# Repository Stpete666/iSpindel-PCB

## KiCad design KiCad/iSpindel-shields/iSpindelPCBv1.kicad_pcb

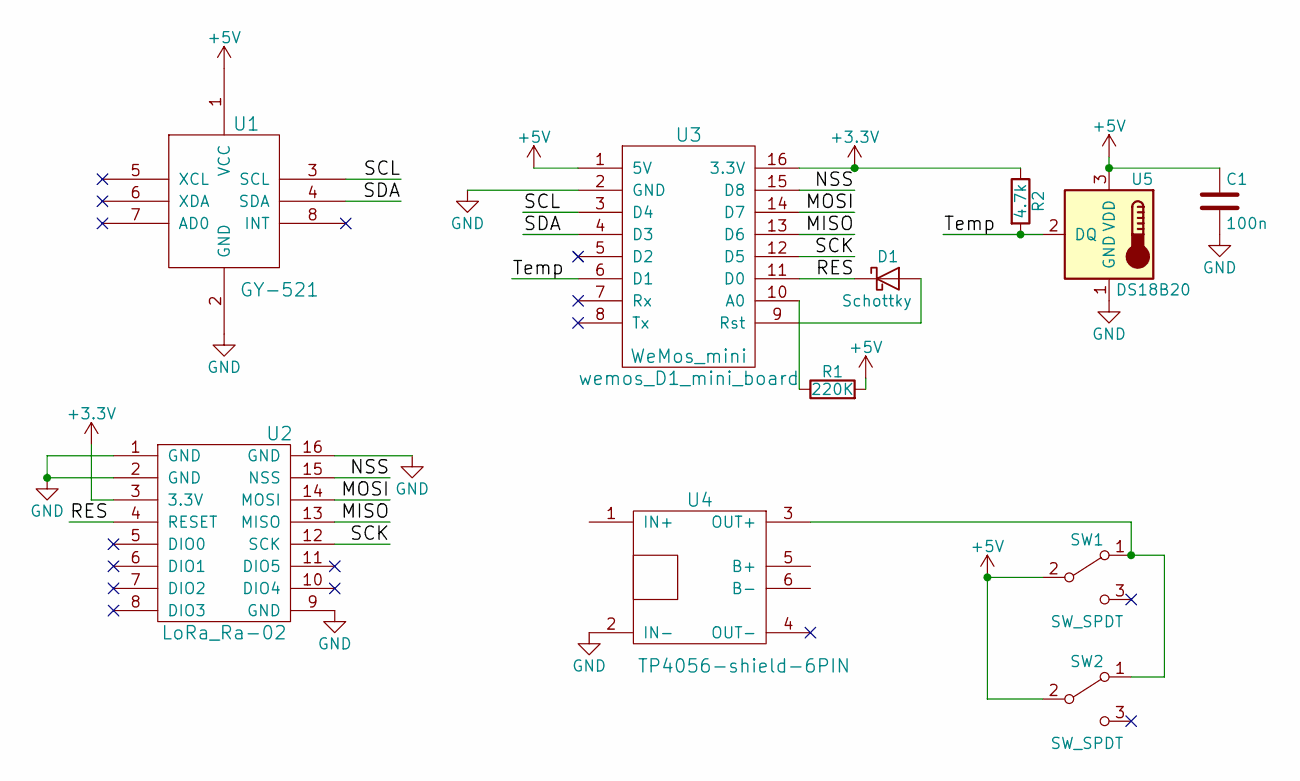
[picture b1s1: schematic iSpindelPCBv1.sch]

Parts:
C1: 100n; C_0805_HandSoldering
D1: Schottky; Resistor_SMD+THTuniversal_0805to1206_RM10_HandSoldering
R1: 220K; Resistor_SMD+THTuniversal_0805to1206_RM10_HandSoldering
R2: 4.7k; Resistor_SMD+THTuniversal_0805to1206_RM10_HandSoldering
SW1: SW_SPDT; SK12D07VG3
SW2: SW_SPDT; SS-12F23
U1: GY-521
U2: LoRa_Ra-02
U3: WeMos_mini; wemos_D1_mini_board
U4: TP4056-shield-6PIN
U5: DS18B20; TO-92_Inline_Narrow_Oval

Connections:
+3V3: R2.1, U2.3 (3.3V), U3.16 (3.3V)
+5V: C1.1, R1.2, SW1.2 (B), SW2.2 (B), U1.1 (VCC), U3.1 (5V), U5.3 (VDD)
/MISO: U2.13 (MISO), U3.13 (D6)
/MOSI: U2.14 (MOSI), U3.14 (D7)
/NSS: U2.15 (NSS), U3.15 (D8)
/RES: D1.1 (K), U2.4 (RESET), U3.11 (D0)
/SCK: U2.12 (SCK), U3.12 (D5)
/SCL: U1.3 (SCL), U3.3 (D4)
/SDA: U1.4 (SDA), U3.4 (D3)
/Temp: R2.2, U3.6 (D1), U5.2 (DQ)
GND: C1.2, U1.2 (GND), U2.1 (GND), U2.2 (GND), U2.9 (GND), U2.16 (GND), U3.2 (GND), U4.2 (IN-), U5.1 (GND)
unnamed: D1.2 (A), U3.9 (Rst)
unnamed: R1.1, U3.10 (A0)
unnamed: SW1.1 (A), SW2.1 (A), U4.3 (OUT+)

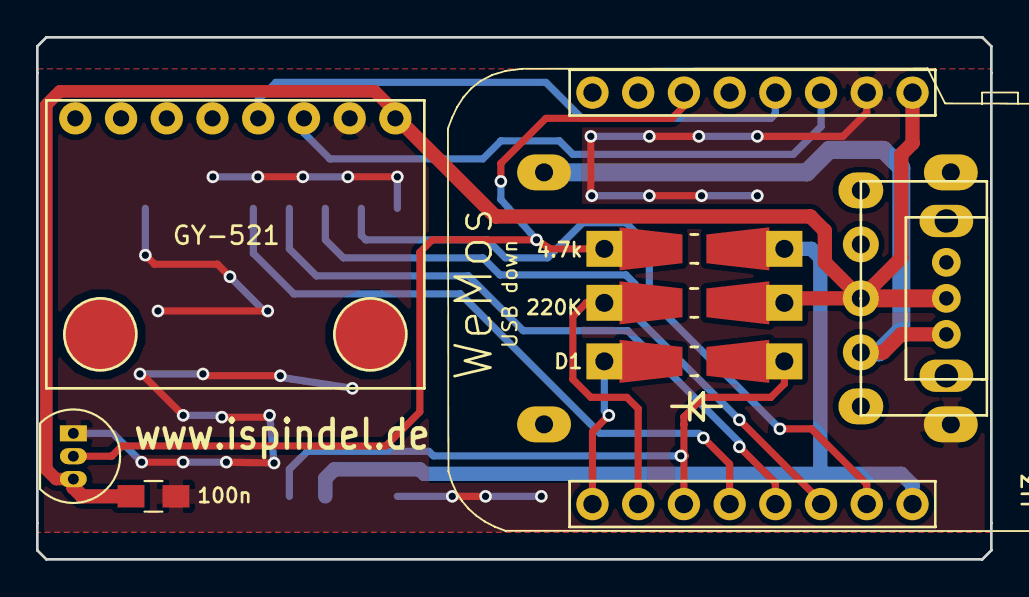
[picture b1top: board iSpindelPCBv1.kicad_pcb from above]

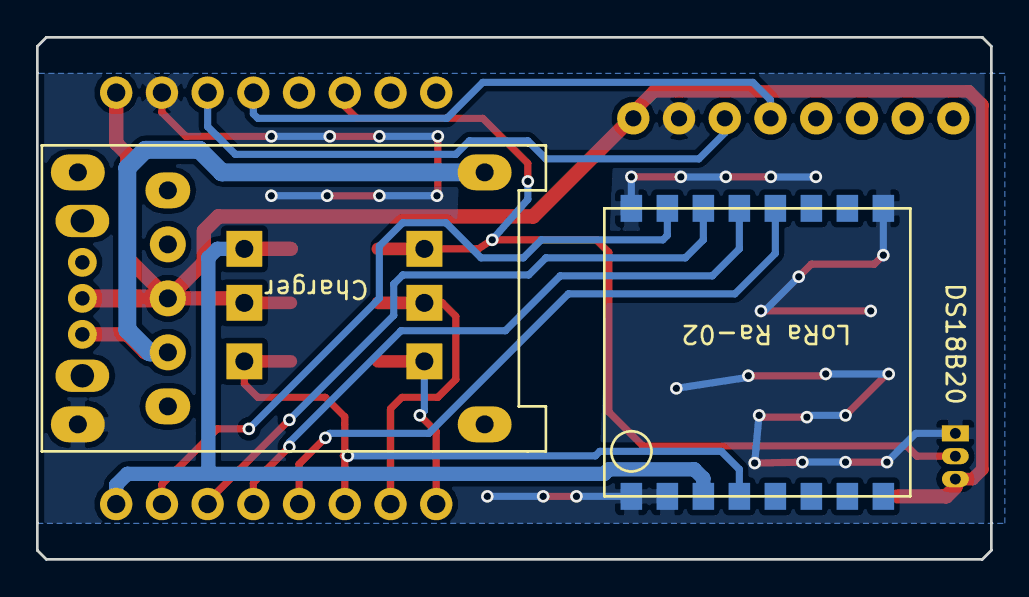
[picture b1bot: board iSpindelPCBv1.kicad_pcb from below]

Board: 2 copper layers, 53.0 x 29.0 mm, 11 parts (2 on the bottom side), 14 nets.

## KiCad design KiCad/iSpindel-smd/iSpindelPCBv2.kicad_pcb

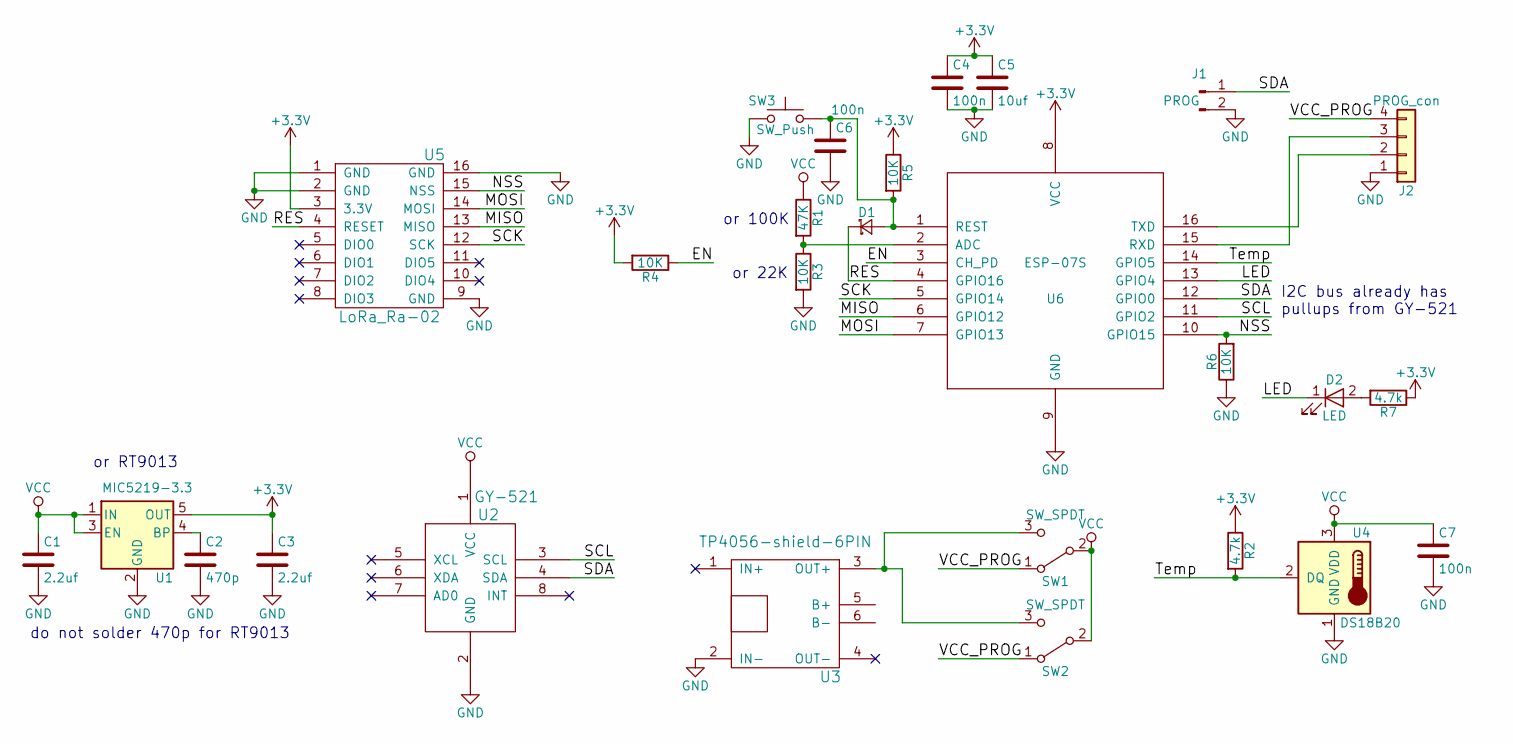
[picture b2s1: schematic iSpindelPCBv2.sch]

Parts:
C1, C3: 2.2uf; C_0805
C2: 470p; C_0603
C4, C6, C7: 100n; C_0603
C5: 10uf; C_0805
D1: Schottky; D_SOD-323
D2: LED; LED_0805
J1: PROG; Pin_Header_Straight_1x02_Pitch2.54mm
J2: PROG_con; Pin_Header_Straight_1x04_Pitch2.54mm
R1: 47K; R_0603
R2, R7: 4.7k; R_0603
R3, R4, R5, R6: 10K; R_0603
SW1: SW_SPDT; SK12D07VG3
SW2: SW_SPDT; SS-12F23
SW3: SW_Push; Button_TS-018
U1: MIC5219-3.3; SOT-23-5
U2: GY-521
U3: TP4056-shield-6PIN
U4: DS18B20; TO-92_Inline_Narrow_Oval
U5: LoRa_Ra-02
U6: ESP-07S

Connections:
+3V3: C3.1, C4.1, C5.1, R2.1, R4.2, R5.1, R7.1, U1.5 (OUT), U5.3 (3.3V), U6.8 (VCC)
/EN: R4.1, U6.3 (CH_PD)
/LED: D2.1 (K), U6.13 (GPIO4)
/MISO: U5.13 (MISO), U6.6 (GPIO12)
/MOSI: U5.14 (MOSI), U6.7 (GPIO13)
/NSS: R6.2, U5.15 (NSS), U6.10 (GPIO15)
/RES: D1.1 (K), U5.4 (RESET), U6.4 (GPIO16)
/SCK: U5.12 (SCK), U6.5 (GPIO14)
/SCL: U2.3 (SCL), U6.11 (GPIO2)
/SDA: J1.1, U2.4 (SDA), U6.12 (GPIO0)
/Temp: R2.2, U4.2 (DQ), U6.14 (GPIO5)
/VCC_PROG: J2.4, SW1.1 (A), SW2.1 (A)
GND: C1.2, C2.2, C3.2, C4.2, C5.2, C6.2, C7.2, J1.2, J2.1, R3.2, R6.1, SW3.2, U1.2 (GND), U2.2 (GND), U3.2 (IN-), U4.1 (GND), U5.1 (GND), U5.2 (GND), U5.9 (GND), U5.16 (GND), U6.9 (GND)
unnamed: C2.1, U1.4 (BP)
unnamed: C6.1, D1.2 (A), R5.2, SW3.1, U6.1 (REST)
unnamed: D2.2 (A), R7.2
unnamed: J2.2, U6.16 (TXD)
unnamed: J2.3, U6.15 (RXD)
unnamed: R1.2, R3.1, U6.2 (ADC)
unnamed: SW1.3 (C), SW2.3 (C), U3.3 (OUT+)
VCC: C1.1, C7.1, R1.1, SW1.2 (B), SW2.2 (B), U1.1 (IN), U1.3 (EN), U2.1 (VCC), U4.3 (VDD)

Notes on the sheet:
or RT9013
do not solder 470p for RT9013
I2C bus already has pullups from GY-521
or 100K
or 22K

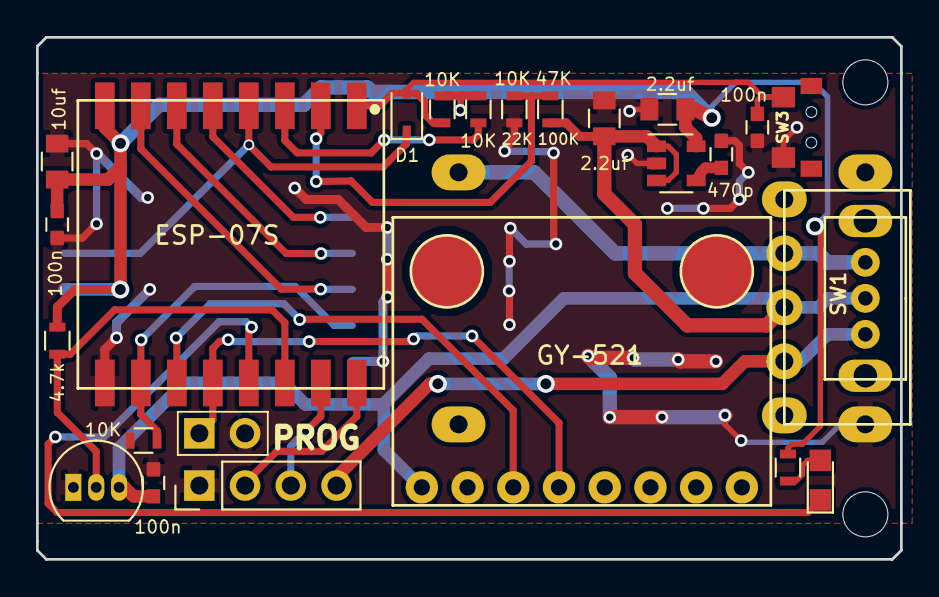
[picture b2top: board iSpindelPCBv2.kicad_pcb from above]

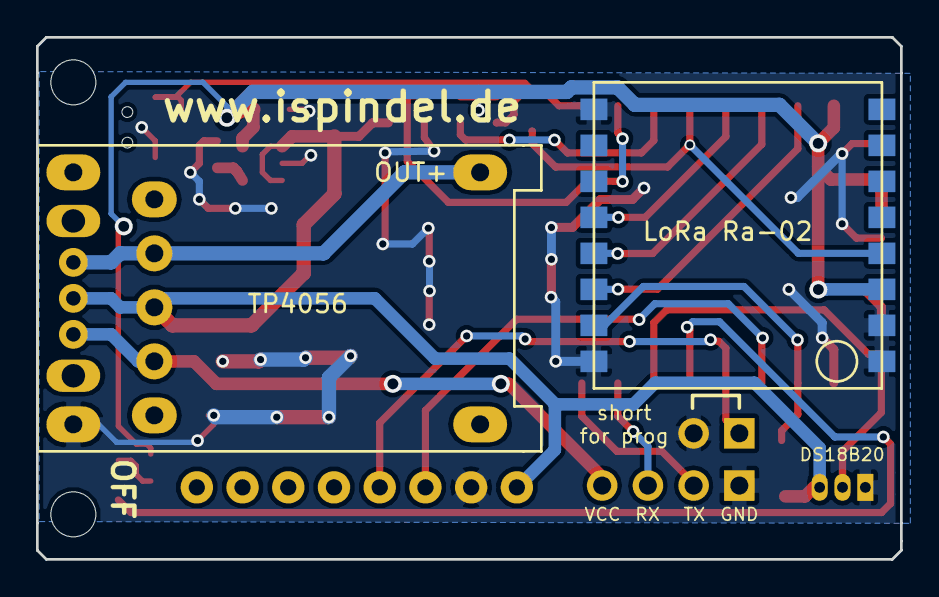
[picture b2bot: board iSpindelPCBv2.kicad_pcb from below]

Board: 2 copper layers, 48.0 x 29.0 mm, 27 parts (2 on the bottom side), 21 nets.

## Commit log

2018-07-20 initial
2018-07-22 Drafts are ready
2018-07-23 small fix
2018-07-24 charger 3d model
2018-07-24 adjust switch and charger
2018-07-24 Some work still in progress
2018-07-25 adjusted some tracks
2018-07-25 Add TH variant
2018-07-26 Last changes
2018-07-26 panel PCBs
2018-07-27 Add led
2018-07-28 Added 3d model for push buttons
2018-08-15 Changed schottky size
2018-08-15 Some minor adjustments to PCB. Added capacitor to DS
